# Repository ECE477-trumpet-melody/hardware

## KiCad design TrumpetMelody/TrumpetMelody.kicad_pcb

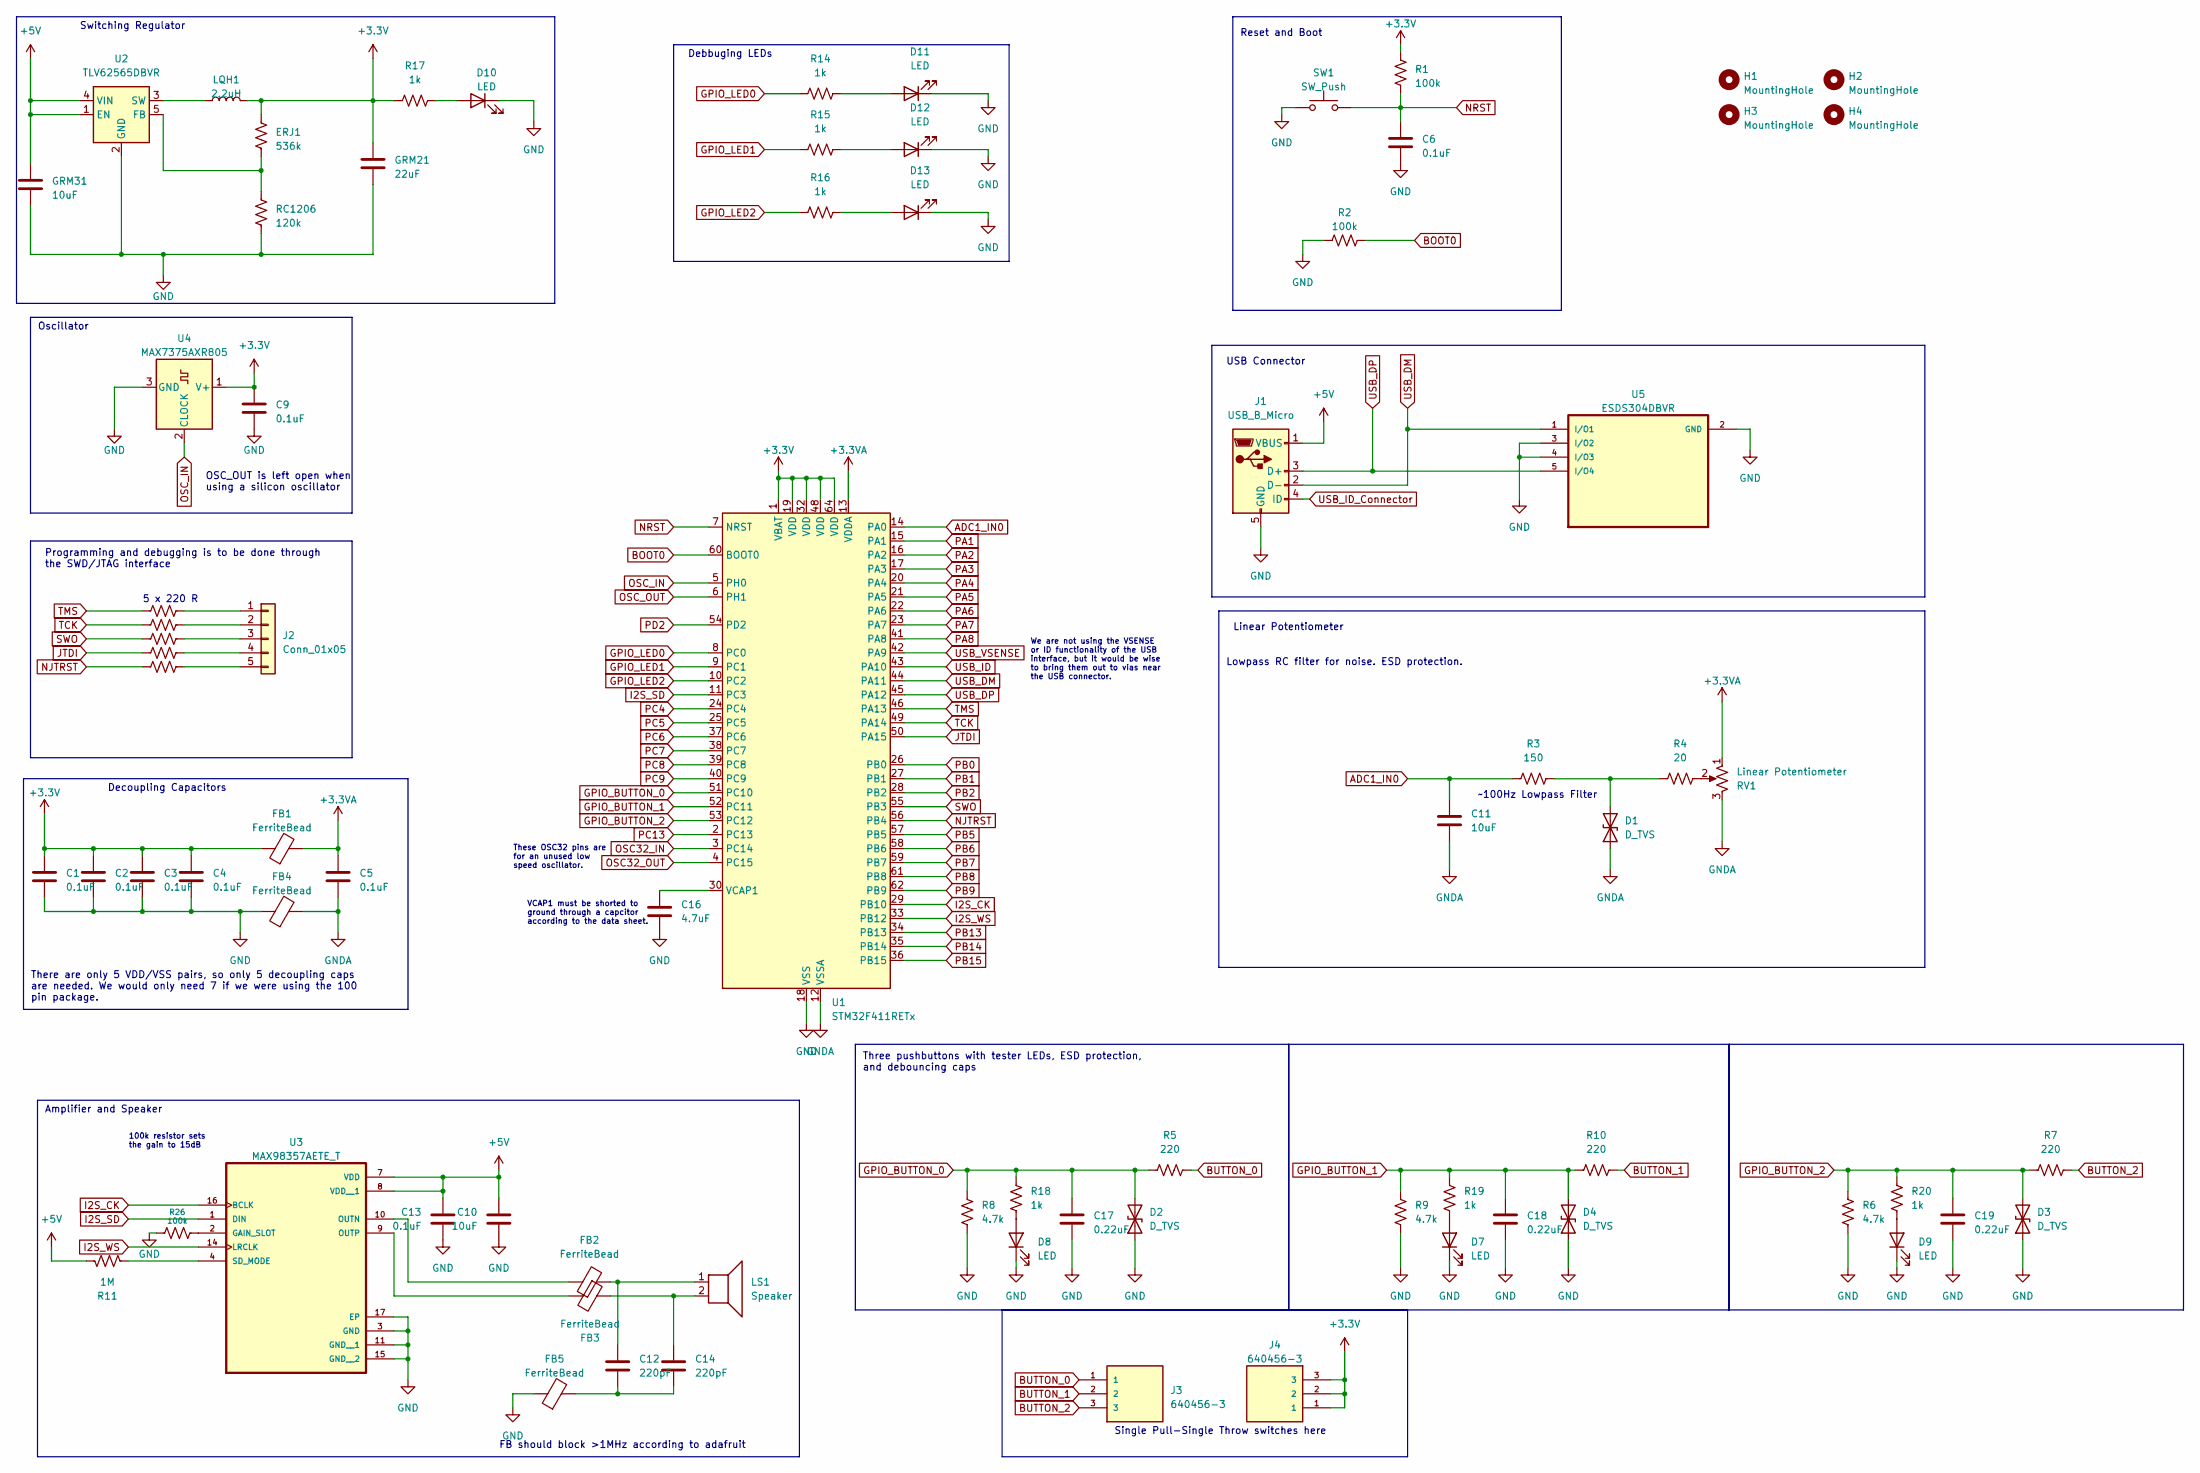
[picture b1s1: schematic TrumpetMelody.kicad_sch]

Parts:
C1, C2, C3, C4, C5, C6, C9, C13: 0.1uF; C_0805_2012Metric_Pad1.18x1.45mm_HandSolder
C10, C11: 10uF; C_0805_2012Metric_Pad1.18x1.45mm_HandSolder
C12, C14: 220pF; C_0805_2012Metric_Pad1.18x1.45mm_HandSolder
C16: 4.7uF; C_0805_2012Metric_Pad1.18x1.45mm_HandSolder
C17, C18, C19: 0.22uF; C_0805_2012Metric_Pad1.18x1.45mm_HandSolder
D1, D2, D3, D4: D_TVS; D_0805_2012Metric
D7, D8, D9, D10, D11, D12, D13: LED; LED_0805_2012Metric_Pad1.15x1.40mm_HandSolder
ERJ1: 536k; R_0805_2012Metric_Pad1.20x1.40mm_HandSolder
FB1, FB2, FB3, FB4, FB5: FerriteBead; FB_LI0805G201R-10
GRM21: 22uF; C_0805_2012Metric_Pad1.18x1.45mm_HandSolder
GRM31: 10uF; C_1206_3216Metric_Pad1.33x1.80mm_HandSolder
H1, H2, H3, H4: MountingHole; MountingHole_3.5mm
J1: USB_B_Micro; TE_2172034-1
J2: Conn_01x05; PinHeader_1x05_P2.54mm_Vertical
J3, J4: 640456-3; TE_640456-3; PARTREV R
LQH1: 2.2uH; L_Murata_LQH55DN_5.7x5.0mm
LS1: Speaker; TE_640456-3
R1, R2, R26: 100k; R_0805_2012Metric_Pad1.20x1.40mm_HandSolder
R3: 150; R_0805_2012Metric_Pad1.20x1.40mm_HandSolder
R4: 20; R_0805_2012Metric_Pad1.20x1.40mm_HandSolder
R5, R7, R10, R21, R22, R23, R24, R25: 220; R_0805_2012Metric_Pad1.20x1.40mm_HandSolder
R6, R8, R9: 4.7k; R_0805_2012Metric_Pad1.20x1.40mm_HandSolder
R11: 1M; R_0805_2012Metric_Pad1.20x1.40mm_HandSolder
R14, R15, R16, R17, R18, R19, R20: 1k; R_0805_2012Metric_Pad1.20x1.40mm_HandSolder
RC1206: 120k; R_1206_3216Metric_Pad1.30x1.75mm_HandSolder
RV1: Linear Potentiometer; TE_640456-3
SW1: SW_Push; SW_SPST_PTS645
U1: STM32F411RETx; LQFP-64_10x10mm_P0.5mm
U2: TLV62565DBVR; SOT-23-5_HandSoldering
U3: MAX98357AETE_T; 21-0136I_T1633-4_MXM-M
U4: MAX7375AXR805; SOT-323_SC-70
U5: ESDS304DBVR; SOT95P280X145-5N

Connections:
+3.3V: C1.1, C2.1, C3.1, C4.1, C9.1, ERJ1.1, FB1.1, GRM21.1, J4.1, J4.2, J4.3, LQH1.2, R1.1, R17.1, U1.1 (VBAT), U1.19 (VDD), U1.32 (VDD), U1.48 (VDD), U1.64 (VDD), U4.1 (V+)
+3.3VA: C5.1, FB1.2, RV1.1, U1.13 (VDDA)
+5V: C10.1, C13.1, GRM31.1, J1.1 (VBUS), R11.1, U2.1 (EN), U2.4 (VIN), U3.7 (VDD), U3.8 (VDD__1)
ADC1_IN0: C11.1, R3.1, U1.14 (PA0)
BOOT0: R2.2, U1.60 (BOOT0)
BUTTON_0: J3.1, R5.2
BUTTON_1: J3.2, R10.2
BUTTON_2: J3.3, R7.2
GND: C1.2, C2.2, C3.2, C4.2, C6.2, C9.2, C10.2, C13.2, C16.2, C17.2, C18.2, C19.2, D2.1 (A1), D3.1 (A1), D4.1 (A1), D7.1 (K), D8.1 (K), D9.1 (K), D10.1 (K), D11.1 (K), D12.1 (K), D13.1 (K), FB4.1, FB5.1, GRM21.2, GRM31.2, J1.5 (GND), R2.1, R6.1, R8.1, R9.1, R26.1, RC1206.2, SW1.1, U1.18 (VSS), U1.31 (VSS), U1.47 (VSS), U1.63 (VSS), U2.2 (GND), U3.3 (GND), U3.11 (GND__1), U3.15 (GND__2), U3.17 (EP), U4.3 (GND), U5.2 (GND), U5.3 (I/O2), U5.4 (I/O3); also elsewhere on the board
GNDA: C5.2, C11.2, D1.1 (A1), FB4.2, RV1.3, U1.12 (VSSA)
GPIO_BUTTON_0: C17.1, D2.2 (A2), R5.1, R8.2, R18.2, U1.51 (PC10)
GPIO_BUTTON_1: C18.1, D4.2 (A2), R9.2, R10.1, R19.2, U1.52 (PC11)
GPIO_BUTTON_2: C19.1, D3.2 (A2), R6.2, R7.1, R20.2, U1.53 (PC12)
GPIO_LED0: R14.1, U1.8 (PC0)
GPIO_LED1: R15.1, U1.9 (PC1)
GPIO_LED2: R16.1, U1.10 (PC2)
I2S_CK: U1.29 (PB10), U3.16 (BCLK)
I2S_SD: U1.11 (PC3), U3.1 (DIN)
I2S_WS: U1.33 (PB12), U3.14 (LRCLK)
JTDI: R24.1, U1.50 (PA15)
NJTRST: R25.1, U1.56 (PB4)
NRST: C6.1, R1.2, SW1.2, U1.7 (NRST)
unnamed: C12.1, FB2.2, LS1.1
unnamed: C12.2, C14.2, FB5.2
unnamed: C14.1, FB3.1, LS1.2
unnamed: D1.2 (A2), R3.2, R4.1
unnamed: D7.2 (A), R19.1
unnamed: D8.2 (A), R18.1
unnamed: D9.2 (A), R20.1
unnamed: D10.2 (A), R17.2
unnamed: D11.2 (A), R14.2
unnamed: D12.2 (A), R15.2
unnamed: D13.2 (A), R16.2
unnamed: J2.1, R21.2
unnamed: J2.2, R22.2
unnamed: J2.3, R23.2
unnamed: J2.4, R24.2
unnamed: J2.5, R25.2
unnamed: R4.2, RV1.2
unnamed: C16.1, U1.30 (VCAP1)
unnamed: ERJ1.2, RC1206.1, U2.5 (FB)
unnamed: LQH1.1, U2.3 (SW)
unnamed: R26.2, U3.2 (GAIN_SLOT)
unnamed: FB2.1, U3.10 (OUTN)
unnamed: FB3.2, U3.9 (OUTP)
unnamed: R11.2, U3.4 (SD_MODE)
OSC32_IN: U1.3 (PC14)
OSC32_OUT: U1.4 (PC15)
OSC_IN: U1.5 (PH0), U4.2 (CLOCK)
OSC_OUT: U1.6 (PH1)
PA1: U1.15 (PA1)
PA2: U1.16 (PA2)
PA3: U1.17 (PA3)
PA4: U1.20 (PA4)
PA5: U1.21 (PA5)
PA6: U1.22 (PA6)
PA7: U1.23 (PA7)
PA8: U1.41 (PA8)
PB0: U1.26 (PB0)
PB1: U1.27 (PB1)
PB2: U1.28 (PB2)
PB5: U1.57 (PB5)
PB6: U1.58 (PB6)
PB7: U1.59 (PB7)
PB8: U1.61 (PB8)
PB9: U1.62 (PB9)
PB13: U1.34 (PB13)
PB14: U1.35 (PB14)
PB15: U1.36 (PB15)
PC4: U1.24 (PC4)
PC5: U1.25 (PC5)
PC6: U1.37 (PC6)
PC7: U1.38 (PC7)
PC8: U1.39 (PC8)
PC9: U1.40 (PC9)
PC13: U1.2 (PC13)
PD2: U1.54 (PD2)
SWO: R23.1, U1.55 (PB3)
TCK: R22.1, U1.49 (PA14)
TMS: R21.1, U1.46 (PA13)
USB_DM: J1.2 (D-), U1.44 (PA11), U5.1 (I/O1)
USB_DP: J1.3 (D+), U1.45 (PA12), U5.5 (I/O4)
USB_ID: U1.43 (PA10)
USB_ID_Connector: J1.4 (ID)
USB_VSENSE: U1.42 (PA9)

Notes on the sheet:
USB Connector
Switching Regulator
~100Hz Lowpass Filter
5 x 220 R
Oscillator
FB should block >1MHz according to adafruit
Single Pull-Single Throw switches here
100k resistor sets the gain to 15dB
Amplifier and Speaker
There are only 5 VDD/VSS pairs, so only 5 decoupling caps are needed. We would only need 7 if we were using the 100 pin package.
These OSC32 pins are for an unused low speed oscillator.
OSC_OUT is left open when using a silicon oscillator
Linear Potentiometer
We are not using the VSENSE or ID functionality of the USB interface, but it would be wise to bring them out to vias near the USB connector.
Programming and debugging is to be done through the SWD/JTAG interface
Three pushbuttons with tester LEDs, ESD protection, and debouncing caps
Reset and Boot
Debbuging LEDs
VCAP1 must be shorted to ground through a capcitor according to the data sheet.
Lowpass RC filter for noise. ESD protection.
Decoupling Capacitors

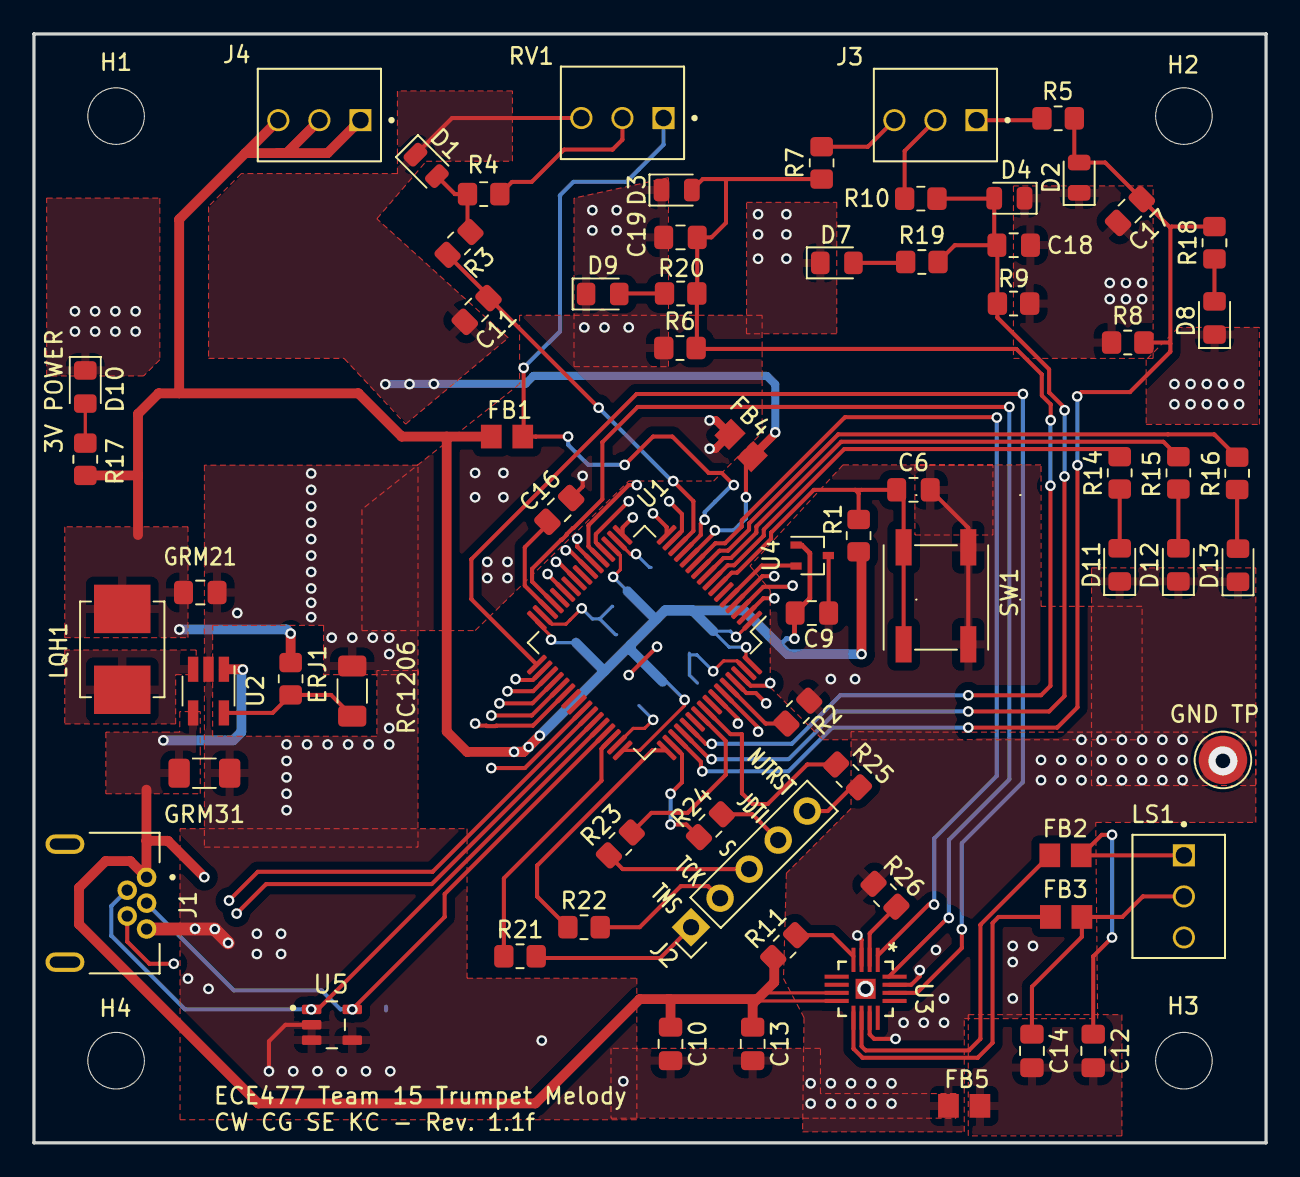
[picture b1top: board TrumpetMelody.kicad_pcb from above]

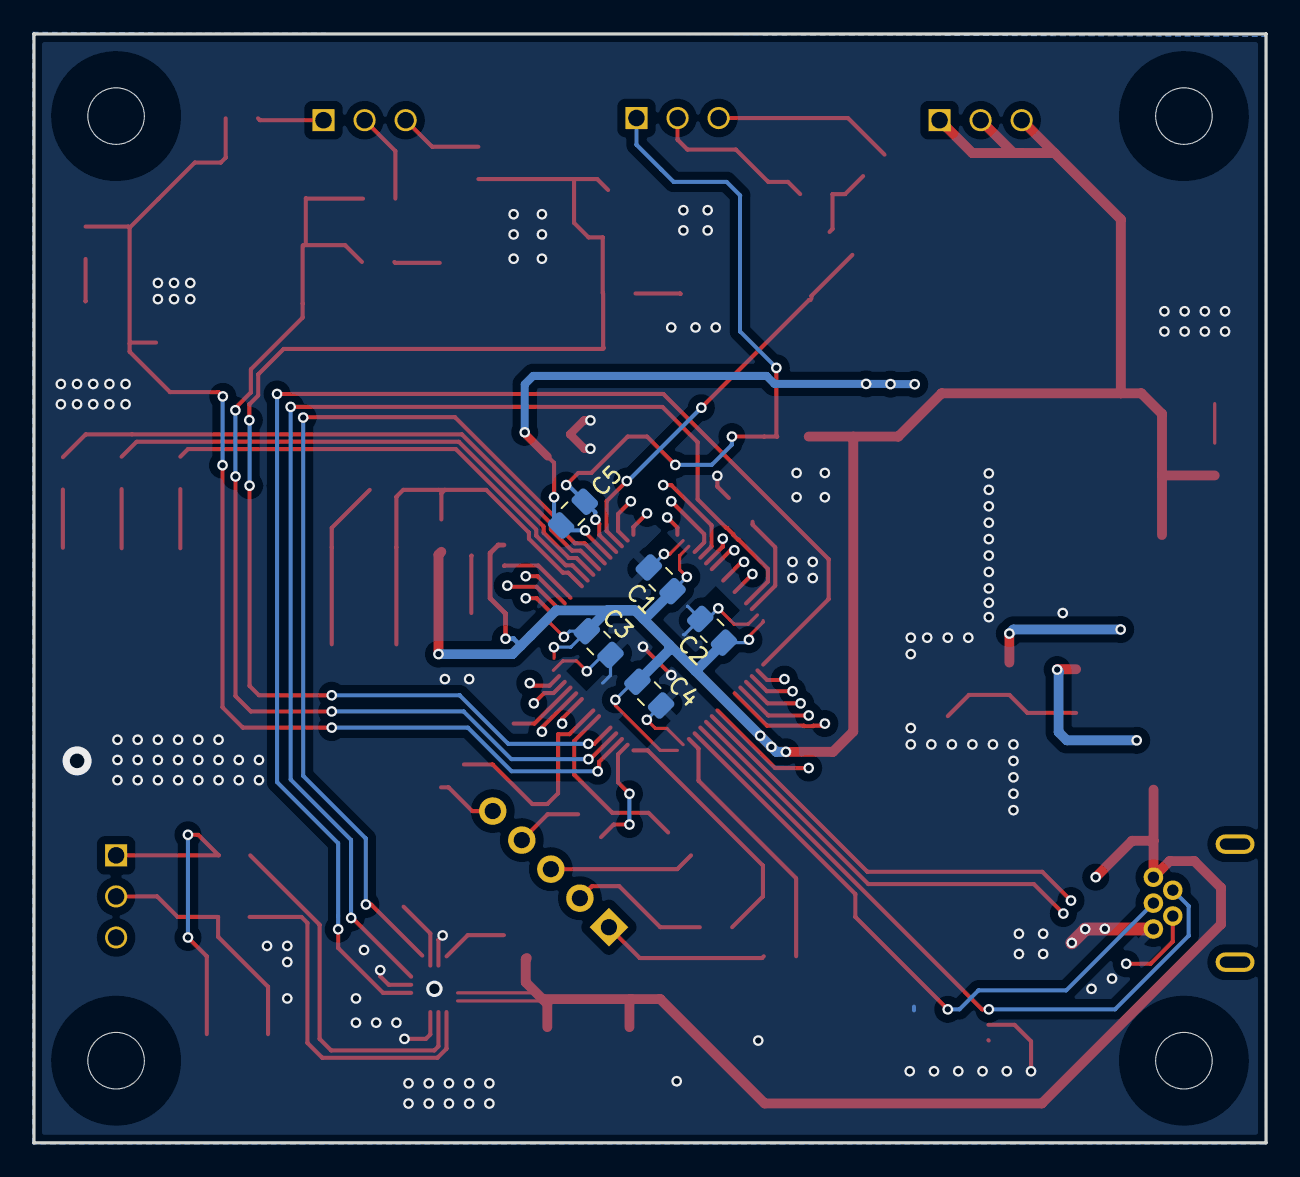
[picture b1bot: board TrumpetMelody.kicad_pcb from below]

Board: 2 copper layers, 76.2 x 68.6 mm, 78 parts (5 on the bottom side), 52 nets.

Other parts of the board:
GND TP: TestPoint_Pad_D3.0mm

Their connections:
GND: GND TP.1; also elsewhere on the board

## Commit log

2024-02-20 Started Design and imported some schematics
    Manually created and scoped out the switching regulator
    Set areas for different parts
    Started work on speakers by importing MAX98357 symbol and creating a project library
2024-02-20 To CLAYTON: Marked some details out for the different components
    Please try to do the things that would be easier for you to do and harder for me to do.
    I.E. USB schem, XTAL schem, marking pins with labels, putting those labels in their corresponding boxes too, programming header.
    I can handle doing the peripherals after getting past pin assignments, I will also try to add some debugging things now, but mostly that will be done during layout.
2024-02-21 Major updates, lots of first draft of components
    Put in XTAL, did a bunch of research on how to select the capacitors but it comes down to actually picking an oscillator to use, we forgot to order one.
    Accidentally ran into the USB micro connector schematic and that was super easy, but we might need to modify for ESD and shielding.
    Tried to do the programming pins, but I had trouble finding something on how those work and how we will do it, Clayton can probably handle that another time.
    Added linear potentiometer leading into 100Hz lowpass filter, and ESD
    Added buttons with ESD
2024-02-21 Added speakers and amplifier
    Yeah i think this is fine for now
2024-02-21 made manlab changes
2024-02-21 Added debugging LEDs
2024-02-21 edits to button tester LEDs & positioning
2024-02-21 edited more LEDs
2024-02-22 Added labels to every pin
2024-02-23 Added gain resistor to speaker circuit
2024-02-23 Added debouncing caps to the buttons
2024-02-23 Added oscillator
2024-02-23 test
2024-02-23 finished schematic and intialized PCB
2024-02-23 set board parameters (poorly) and put some stuff in rought spacing
2024-02-24 Fixed grounds on the speaker and potentiometer
2024-02-24 switching regulator/USB in place, some silkscreen stuff, defined edges
2024-02-24 modifying some regulator placement
2024-02-24 more changes to 5V side
2024-02-25 Added decoupling caps to the micro
2024-02-25 condensed 5V side
2024-02-26 more 3V stuff added in, nearly done micro connections
2024-02-26 everything onboard except for the buttons- see notes on pcb drawing.
2024-02-26 changes to notes
2024-02-26 Added power bus to micro side
2024-02-26 put the FBs and the button components on the board.
2024-02-27 Changed +3.3V on the poteniometer to +3.3VA
2024-02-27 Slight change to the 3.3VA decoupling cap
2024-02-27 Fixed poteniometer power line
2024-02-27 changed 5V line a little, changed a signal crossing
2024-02-27 usb signal slight change
2024-02-27 slight changes to a resistor positioning
2024-02-27 i am going to scream why do the silkscreen references keep changing
2024-02-27 silkscreen >:(
2024-02-27 Manually added TI Webench PCB layout
    I just sort of rotated the picture and drew it on
    There's a bunch of holes in the PCB layout and I don't know if those are supposed to be vias or whatever. I may have used the wrong type of hole to switch board sides too.
2024-02-27 a diode on the linear pot got disconnected so i reconnected it
2024-02-27 Added stitching vias
2024-02-27 Placed vias so we can connect USB_ID and USB_VSENSE later if needed
2024-02-27 Initialized GND Planes and tweaked stitching vias
2024-02-28 slight wire changes and connected some of the ground bus to the usb input ground
2024-02-28 public enemy #1: analog ground
2024-02-28 Added FB to simplify AGND
2024-02-28 Updated TVS Diodes to be right size and fixed placements
2024-02-28 slight adjustment
2024-02-28 Added GND plane to amplifier circuitry
2024-02-28 Added a bunch of ground planes
2024-02-28 Added a ground test point
2024-02-28 Pulled out most of the GPIO pins to vias
2024-02-28 Fixed the analog ground on the micro
2024-02-28 Fixed DRC errors
2024-02-28 Printed Schematic Out
2024-02-28 via sizes
2024-02-28 labels
2024-02-28 Removed question marks from schematic
2024-02-29 zip file
2024-02-29 slight wiring modifications
2024-02-29 modified the USB traces bc one of the turns was too turney
2024-02-29 i have no idea what change this was but its there
2024-02-29 need to fix DRC issues soon
2024-03-06 trying to fix sync
2024-03-06 tbd list readded with things that need to be done
2024-03-06 modified the DRC rules based on jlcpcb minimums and DRC lit up like a christmas tree so i will be slowly going through that stuff
2024-03-06 christmas tree of DRC pointers
2024-03-06 finished DRC complaints pls verify the last warning ty
2024-03-06 i will fight the DRC
2024-03-06 something autorouted and i just noticed it but now it is fixed
2024-03-06 Fixed a right angle
2024-03-06 changed some traces
2024-03-06 changed
2024-03-06 added alligator
2024-03-06 cleaning
2024-03-06 Finished PCB
2024-03-06 Minor edits
2024-03-07 Changed button footprint and verified design
2024-03-07 New ESD protection on USB and verified
2024-03-07 changes to DP/DM signals to reduce via usage/turns, slight change to the button 0 routing bc i saw an acute angle
2024-03-08 adjusted one trace
2024-03-08 Readded? gerbers, there should have been some already
    only did the basic plot gerber, also made sure to not tent vias
2024-03-08 Made ground trace larger
2024-03-08 Updated PCB on website
